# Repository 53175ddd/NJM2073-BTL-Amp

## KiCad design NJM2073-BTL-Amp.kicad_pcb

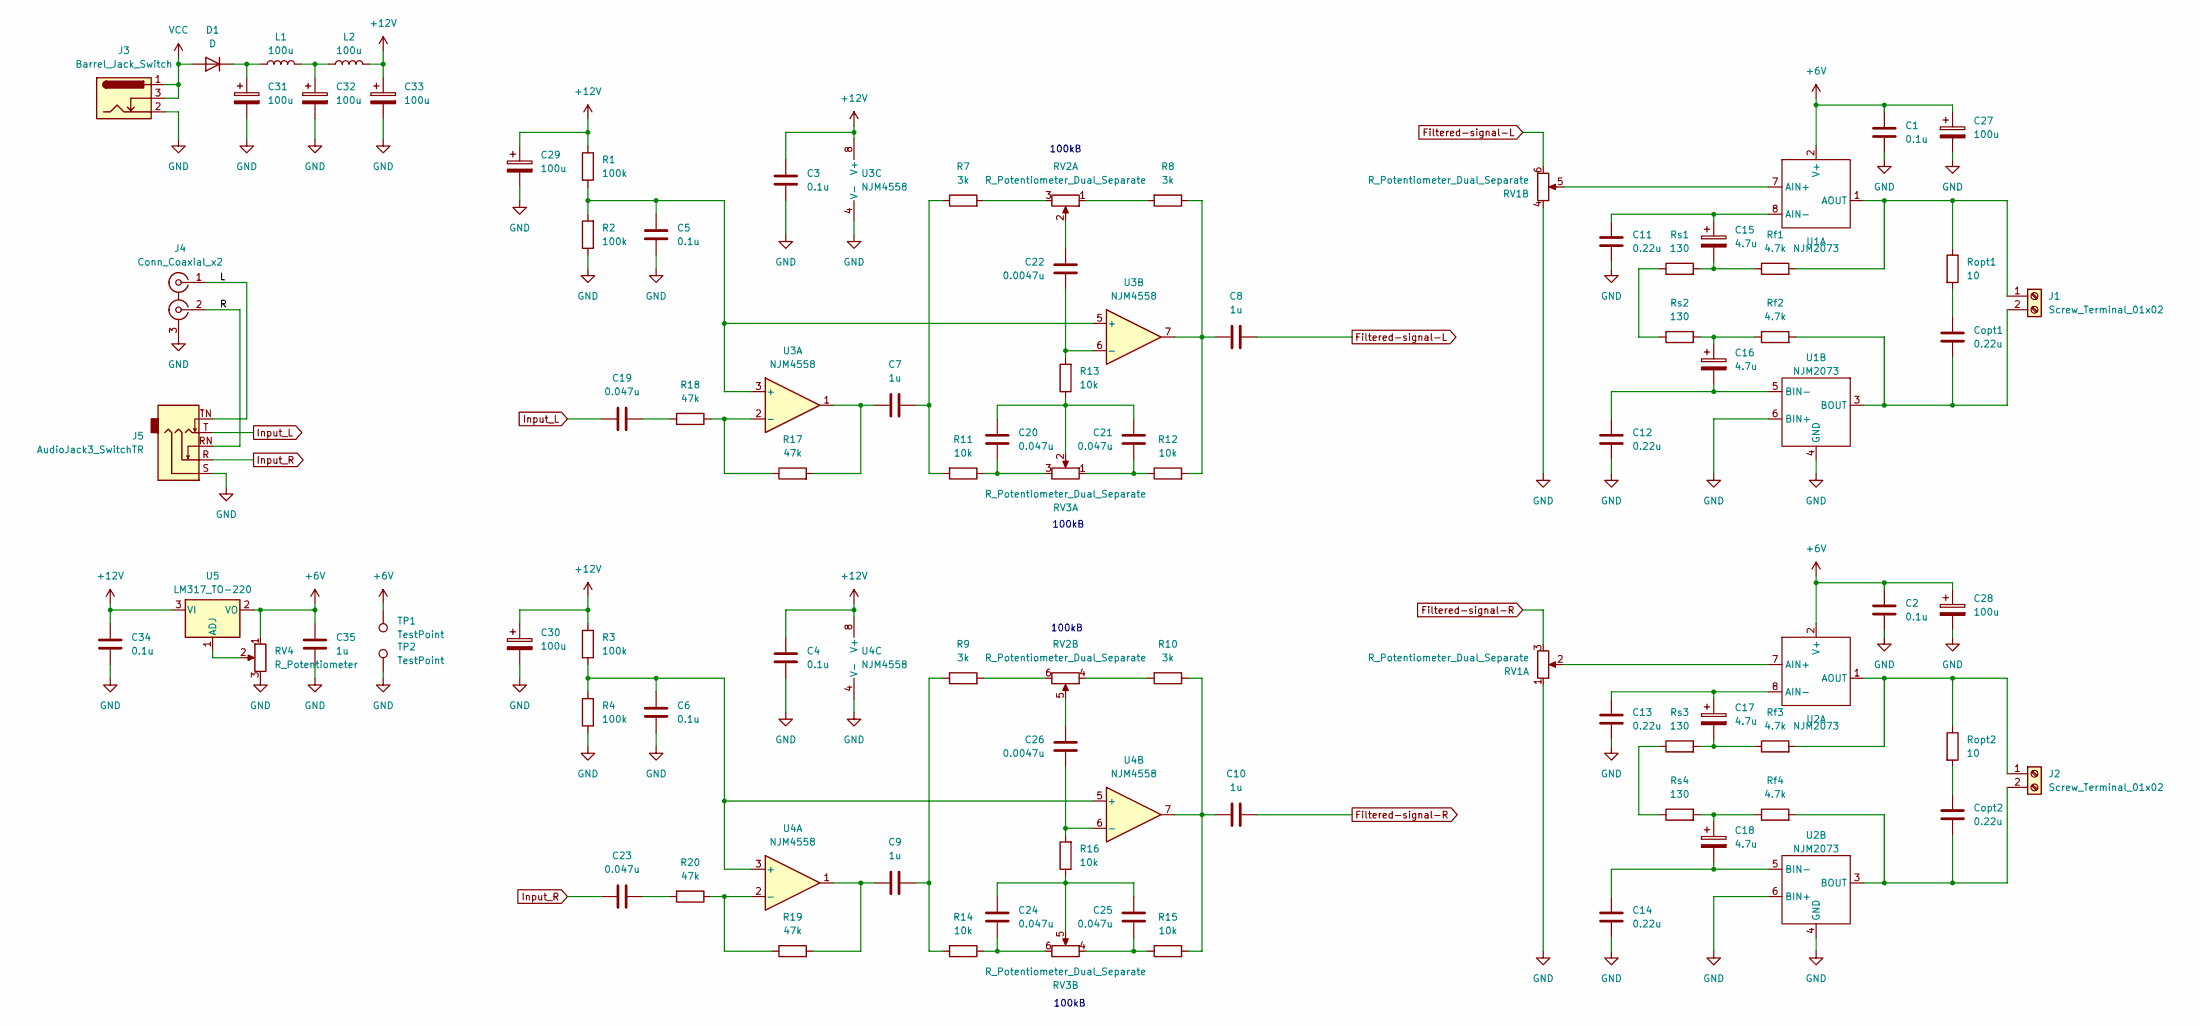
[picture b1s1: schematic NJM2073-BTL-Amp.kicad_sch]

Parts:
C1, C2, C3, C4, C5, C6, C34: 0.1u; C_Disc_D5.0mm_W2.5mm_P5.00mm
C7, C8, C9, C10: 1u; CP_Radial_D5.0mm_P2.00mm
C11, C12, C13, C14: 0.22u; C_Disc_D5.0mm_W2.5mm_P5.00mm
C15, C16, C17, C18: 4.7u; C_Disc_D5.0mm_W2.5mm_P5.00mm
C19, C20, C21, C23, C24, C25: 0.047u; C_Disc_D5.0mm_W2.5mm_P5.00mm
C22, C26: 0.0047u; C_Disc_D5.0mm_W2.5mm_P5.00mm
C27, C28, C29, C30, C31, C32, C33: 100u; CP_Radial_D6.3mm_P2.50mm
C35: 1u; C_Disc_D5.0mm_W2.5mm_P5.00mm
Copt1, Copt2: 0.22u; C_Disc_D5.0mm_W2.5mm_P5.00mm
D1: D; D_A-405_P12.70mm_Horizontal
J1, J2: Screw_Terminal_01x02; PhoenixContact_MCV_1,5_2-G-5.08_1x02_P5.08mm_Vertical
J3: Barrel_Jack_Switch; BarrelJack_Horizontal
J4: Conn_Coaxial_x2; MJ-519
J5: AudioJack3_SwitchTR; Jack_3.5mm_CUI_SJ1-3535NG_Horizontal
L1, L2: 100u; L_Radial_D10.0mm_P5.00mm_Fastron_07M
R1, R2, R3, R4: 100k; R_Axial_DIN0207_L6.3mm_D2.5mm_P10.16mm_Horizontal
R7, R8, R9, R10: 3k; R_Axial_DIN0207_L6.3mm_D2.5mm_P10.16mm_Horizontal
R11, R12, R13, R14, R15, R16: 10k; R_Axial_DIN0207_L6.3mm_D2.5mm_P10.16mm_Horizontal
R17, R18, R19, R20: 47k; R_Axial_DIN0207_L6.3mm_D2.5mm_P10.16mm_Horizontal
RV1, RV2, RV3: R_Potentiometer_Dual_Separate; Potentiometer_Alps_RK097_Dual_Horizontal
RV4: R_Potentiometer; Potentiometer_ACP_CA9-H3,8_Horizontal
Rf1, Rf2, Rf3, Rf4: 4.7k; R_Axial_DIN0207_L6.3mm_D2.5mm_P10.16mm_Horizontal
Ropt1, Ropt2: 10; R_Axial_DIN0207_L6.3mm_D2.5mm_P10.16mm_Horizontal
Rs1, Rs2, Rs3, Rs4: 130; R_Axial_DIN0207_L6.3mm_D2.5mm_P10.16mm_Horizontal
TP1, TP2: TestPoint; TestPoint_Keystone_5000-5004_Miniature
U1, U2: NJM2073; DIP-8_W7.62mm_Socket
U3, U4: NJM4558; DIP-8_W7.62mm_Socket
U5: LM317_TO-220; TO-220-3_Vertical

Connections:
+6V: C1.1, C2.1, C27.1, C28.1, C35.1, RV4.1, TP1.1, U1.2 (V+), U2.2 (V+), U5.2 (VO)
+12V: C3.2, C4.2, C29.1, C30.1, C33.1, C34.1, L2.2, R1.1, R3.1, U3.8 (V+), U4.8 (V+), U5.3 (VI)
/L: J4.1 (IN1), J5.TN
/R: J4.2 (IN2), J5.RN
Filtered-signal-L: C8.2, RV1.6
Filtered-signal-R: C10.2, RV1.3
GND: C1.2, C2.2, C3.1, C4.1, C5.2, C6.2, C11.2, C12.1, C13.2, C14.1, C27.2, C28.2, C29.2, C30.2, C31.2, C32.2, C33.2, C34.2, C35.2, J3.2, J4.3 (EXT), J5.S, R2.1, R4.1, RV1.1, RV1.4, RV4.3, TP2.1, U1.4 (GND), U1.6 (BIN+), U2.4 (GND), U2.6 (BIN+), U3.4 (V-), U4.4 (V-)
Input_L: C19.1, J5.T
Input_R: C23.1, J5.R
unnamed: C7.1, R17.2, U3.1
unnamed: C7.2, R7.1, R11.2
unnamed: C8.1, R8.1, R12.2, U3.7
unnamed: C9.1, R19.2, U4.1
unnamed: C9.2, R9.1, R14.2
unnamed: C10.1, R10.1, R15.2, U4.7
unnamed: C15.2, Rf1.1, Rs1.2
unnamed: C16.1, Rf2.1, Rs2.2
unnamed: C17.2, Rf3.1, Rs3.2
unnamed: C18.1, Rf4.1, Rs4.2
unnamed: C19.2, R18.2
unnamed: C20.1, R11.1, RV3.3
unnamed: C20.2, C21.2, R13.1, RV3.2
unnamed: C21.1, R12.1, RV3.1
unnamed: C22.2, RV2.2
unnamed: C23.2, R20.2
unnamed: C24.1, R14.1, RV3.6
unnamed: C24.2, C25.2, R16.1, RV3.5
unnamed: C25.1, R15.1, RV3.4
unnamed: C26.2, RV2.5
unnamed: C32.1, L1.2, L2.1
unnamed: Copt1.1, Ropt1.2
unnamed: Copt2.1, Ropt2.2
unnamed: C31.1, D1.1 (K), L1.1
unnamed: J1.1, Rf1.2, Ropt1.1, U1.1 (AOUT)
unnamed: Copt1.2, J1.2, Rf2.2, U1.3 (BOUT)
unnamed: J2.1, Rf3.2, Ropt2.1, U2.1 (AOUT)
unnamed: Copt2.2, J2.2, Rf4.2, U2.3 (BOUT)
unnamed: R7.2, RV2.3
unnamed: R8.2, RV2.1
unnamed: R9.2, RV2.6
unnamed: R10.2, RV2.4
unnamed: Rs1.1, Rs2.1
unnamed: Rs3.1, Rs4.1
unnamed: RV1.5, U1.7 (AIN+)
unnamed: C11.1, C15.1, U1.8 (AIN-)
unnamed: C12.2, C16.2, U1.5 (BIN-)
unnamed: RV1.2, U2.7 (AIN+)
unnamed: C13.1, C17.1, U2.8 (AIN-)
unnamed: C14.2, C18.2, U2.5 (BIN-)
unnamed: C5.1, R1.2, R2.2, U3.3 (+), U3.5 (+)
unnamed: R17.1, R18.1, U3.2 (-)
unnamed: C22.1, R13.2, U3.6 (-)
unnamed: C6.1, R3.2, R4.2, U4.3 (+), U4.5 (+)
unnamed: R19.1, R20.1, U4.2 (-)
unnamed: C26.1, R16.2, U4.6 (-)
unnamed: RV4.2, U5.1 (ADJ)
VCC: D1.2 (A), J3.1, J3.3

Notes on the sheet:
100kB

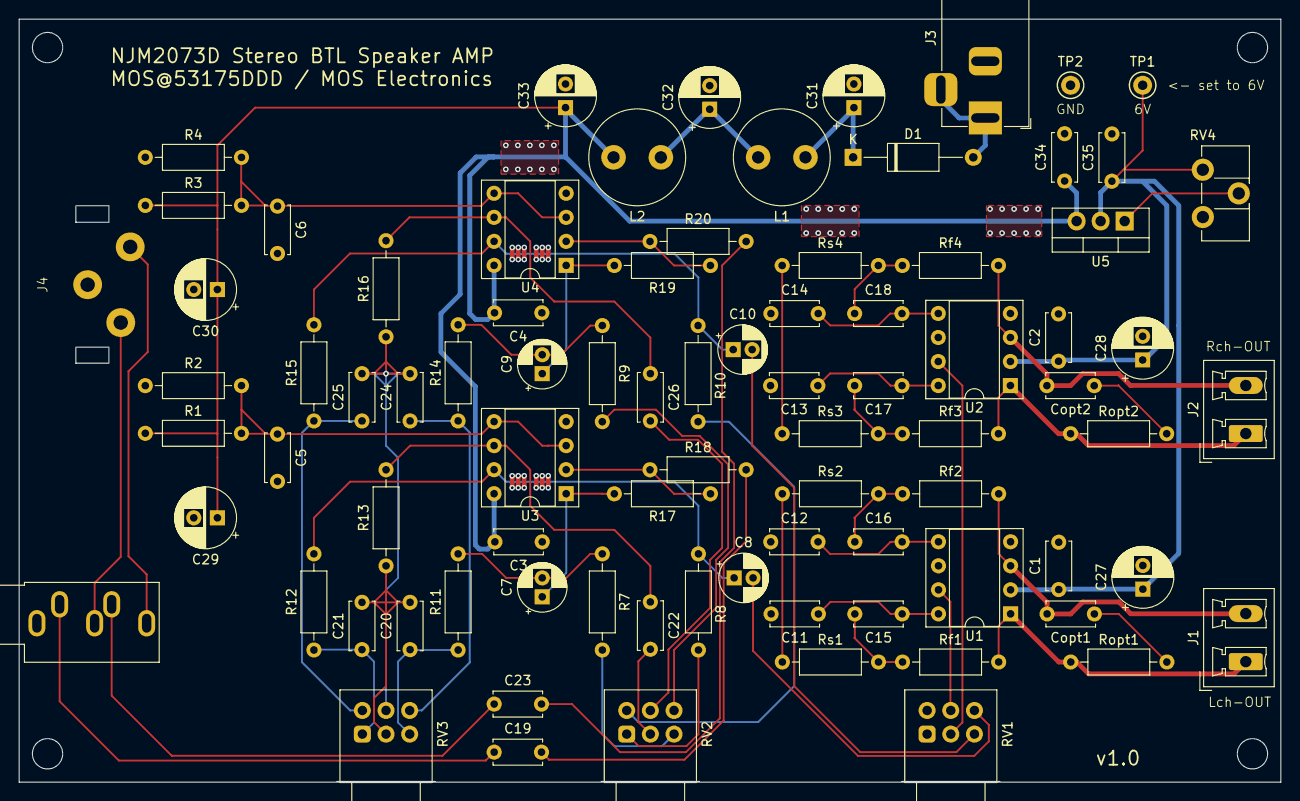
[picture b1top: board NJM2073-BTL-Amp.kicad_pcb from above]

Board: 2 copper layers, 133.3 x 80.6 mm, 84 parts (0 on the bottom side), 57 nets.

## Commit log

2024-12-20 プロジェクト作成
2024-12-21 シンボル作成
2024-12-21 BTL アンプ回路作成
    ゲインは 30dB
2024-12-23 フィルタ回路作成
2024-12-26 電源シンボル移動
2024-12-26 ラベル名変更
2024-12-26 電源入力・フィルタ追加
2024-12-26 逆接保護ダイオード追加
2024-12-26 音声入力追加
2024-12-26 フットプリント割り当て
2024-12-26 フットプリント作成
2024-12-26 フットプリント修正
2024-12-26 シンボル名修正
2024-12-26 2073 の電源回路作成
2024-12-26 フットプリントをアップデート
2024-12-27 除外設定を解除
2024-12-27 フットプリント変更
2024-12-27 部品の向き修正
2024-12-27 BTL アンプ部片チャンネルだけ配置配線
2024-12-27 BTL アンプ部構成・アンプ電源配置配線
2024-12-28 部品結線変更
2024-12-28 基板作成
2024-12-28 ちょっと修正
2024-12-28 シルク印刷追加
2024-12-28 ガーバー出力
2025-01-01 抵抗値修正
2025-01-10 コネクタ穴径修正
2025-01-11 配線修正
2025-01-14 ちょいと修正
